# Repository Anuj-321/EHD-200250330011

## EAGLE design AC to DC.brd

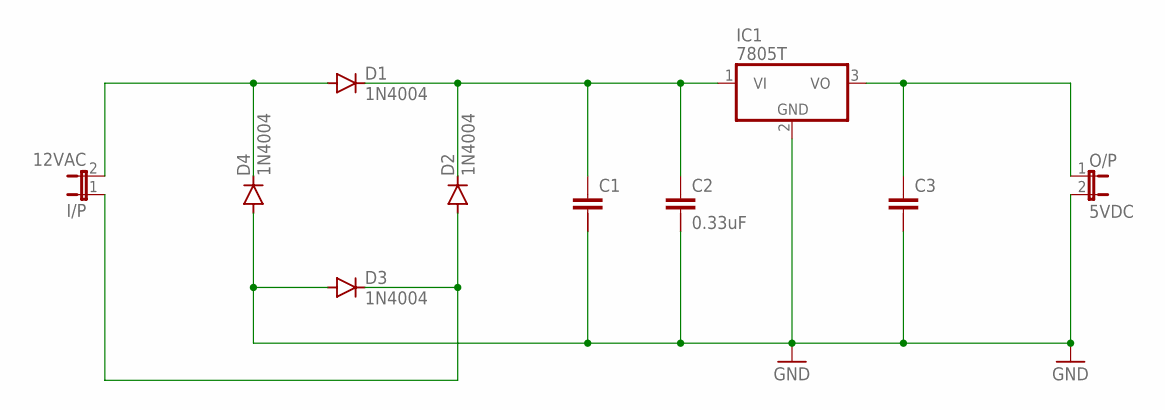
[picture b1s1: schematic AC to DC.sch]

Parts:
C1, C3: C-2.5-5/2; C2.5/5-2
C2: 0.33uF; C2.5/5-2
D1, D2, D3, D4: 1N4004; DO41-10
I/P: 12VAC; JP1
IC1: 7805T; TO220H
O/P: 5VDC; JP1

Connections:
GND: C1.2, C2.2, C3.2, D3.A, D4.A, IC1.2 (GND), O/P.2
unnamed: D1.A, D4.C, I/P.2
unnamed: C1.1, C2.1, D1.C, D2.C, IC1.1 (VI)
unnamed: D2.A, D3.C, I/P.1
unnamed: C3.1, IC1.3 (VO), O/P.1

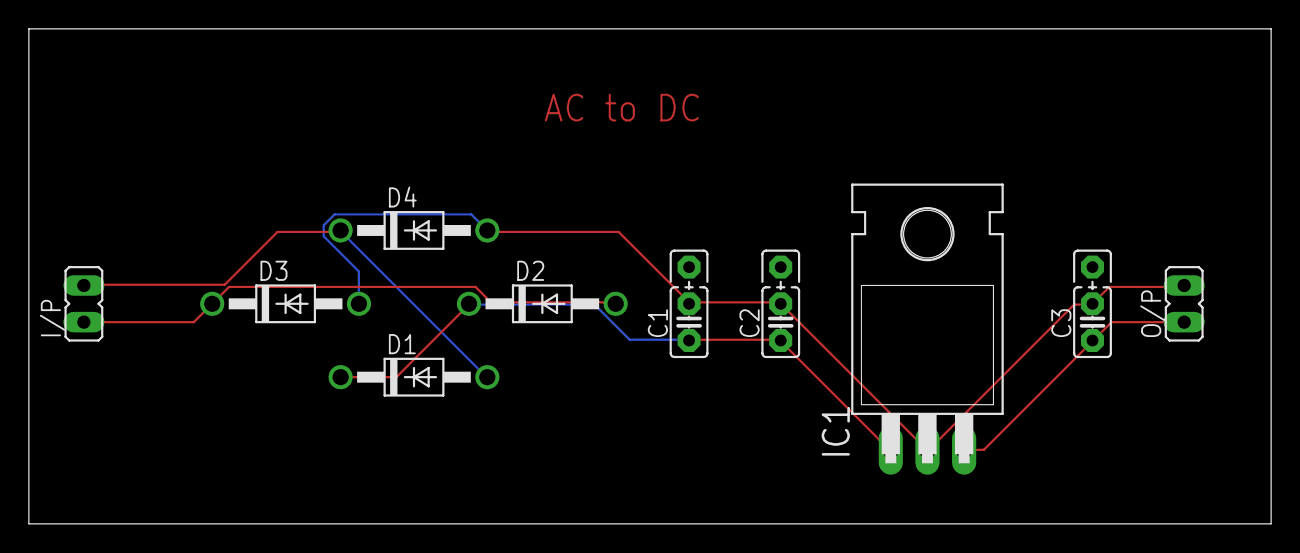
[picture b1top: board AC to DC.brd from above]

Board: 2 copper layers, 86.0 x 34.3 mm, 10 parts (0 on the bottom side), 5 nets.

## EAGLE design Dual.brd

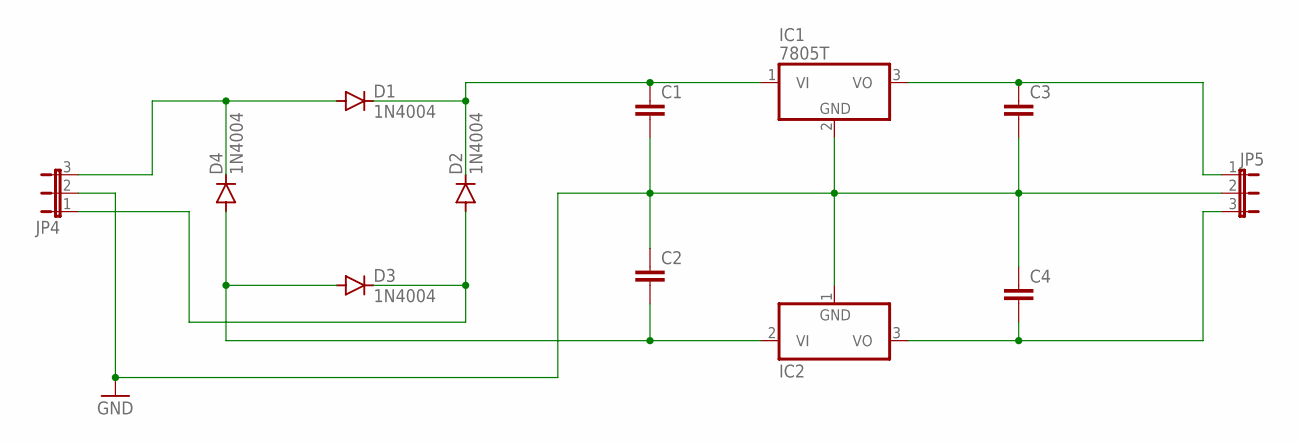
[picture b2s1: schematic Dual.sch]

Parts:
C1, C2, C3, C4: C2,5-3; C2.5-3
D1, D2, D3, D4: 1N4004; DO41-10
IC1: 7805T; TO220H
IC2: 7905T; TO220H
JP4, JP5: JP2W

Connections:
GND: C1.2, C2.1, C3.2, C4.1, IC1.2 (GND), IC2.1 (GND), JP4.2, JP5.2
unnamed: D1.A, D4.C, JP4.3
unnamed: C2.2, D3.A, D4.A, IC2.2 (VI)
unnamed: D2.A, D3.C, JP4.1
unnamed: C1.1, D1.C, D2.C, IC1.1 (VI)
unnamed: C4.2, IC2.3 (VO), JP5.3
unnamed: C3.1, IC1.3 (VO), JP5.1

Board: 2 copper layers, 12 parts (0 on the bottom side), 7 nets, no tracks yet.
